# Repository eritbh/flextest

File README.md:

# flextest

testing flex PCBs for some stuff pls ignore

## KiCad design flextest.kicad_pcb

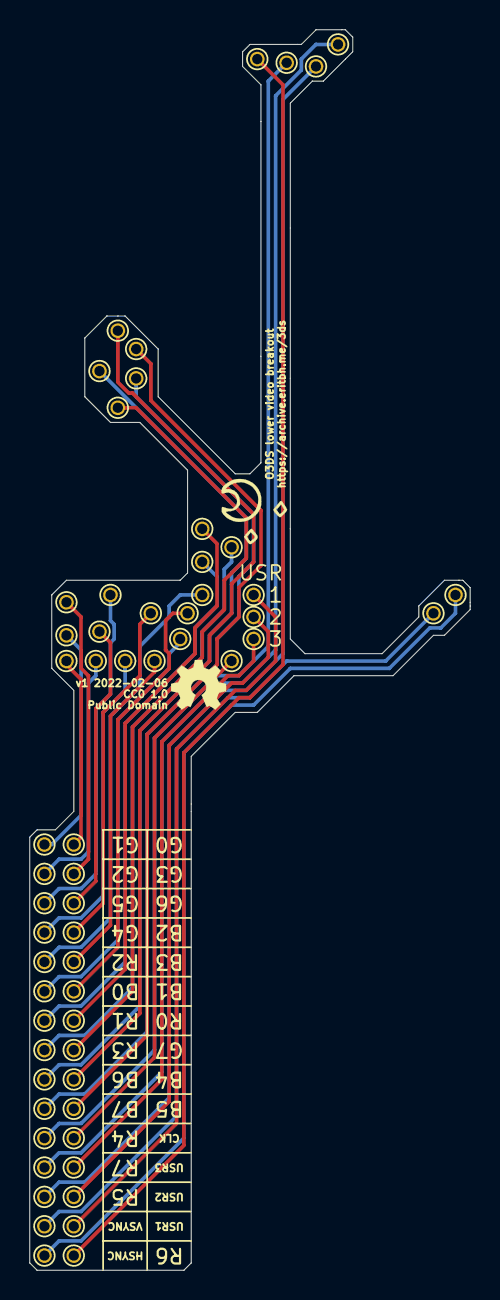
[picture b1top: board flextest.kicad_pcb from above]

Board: 2 copper layers, 30.0 x 84.5 mm, 60 parts (0 on the bottom side), 30 nets.

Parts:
H1, H2, H3, H4, H5, H6, H7, H8, H9, H10, H11, H12, H13, H14, H15, H16, H17, H18, H19, H20, H21, H22, H23, H24, H25, H26, H27, H28, H29, H30, H31, H32, H33, H34, H35, H36, H37, H38, H39, H40, H41, H42, H43, H44, H45, H46, H47, H48, H49, H50, H51, H52, H53, H54, H55, H56, H57, H58, H59, H60: MountingHole_Pad; TestPoint_THTPad_D1.0mm_Drill0.7mm

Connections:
/B0: H47.1, H48.1
/B1: H45.1, H46.1
/B2: H43.1, H44.1
/B3: H41.1, H42.1
/B4: H39.1, H40.1
/B5: H37.1, H38.1
/B6: H35.1, H36.1
/B7: H33.1, H34.1
/CLK: H49.1, H50.1
/G0: H31.1, H32.1
/G1: H29.1, H30.1
/G2: H27.1, H28.1
/G3: H25.1, H26.1
/G4: H23.1, H24.1
/G5: H21.1, H22.1
/G6: H19.1, H20.1
/G7: H17.1, H18.1
/HSYNC: H51.1, H52.1
/R0: H15.1, H16.1
/R1: H13.1, H14.1
/R2: H11.1, H12.1
/R3: H9.1, H10.1
/R4: H7.1, H8.1
/R5: H5.1, H6.1
/R6: H3.1, H4.1
/R7: H1.1, H2.1
/USR1: H55.1, H56.1
/USR2: H57.1, H58.1
/USR3: H59.1, H60.1
/VSYNC: H53.1, H54.1

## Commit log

2022-02-06 Create LICENSE

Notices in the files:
flextest.kicad_pcb:
Public Domain
CC0 1.0
